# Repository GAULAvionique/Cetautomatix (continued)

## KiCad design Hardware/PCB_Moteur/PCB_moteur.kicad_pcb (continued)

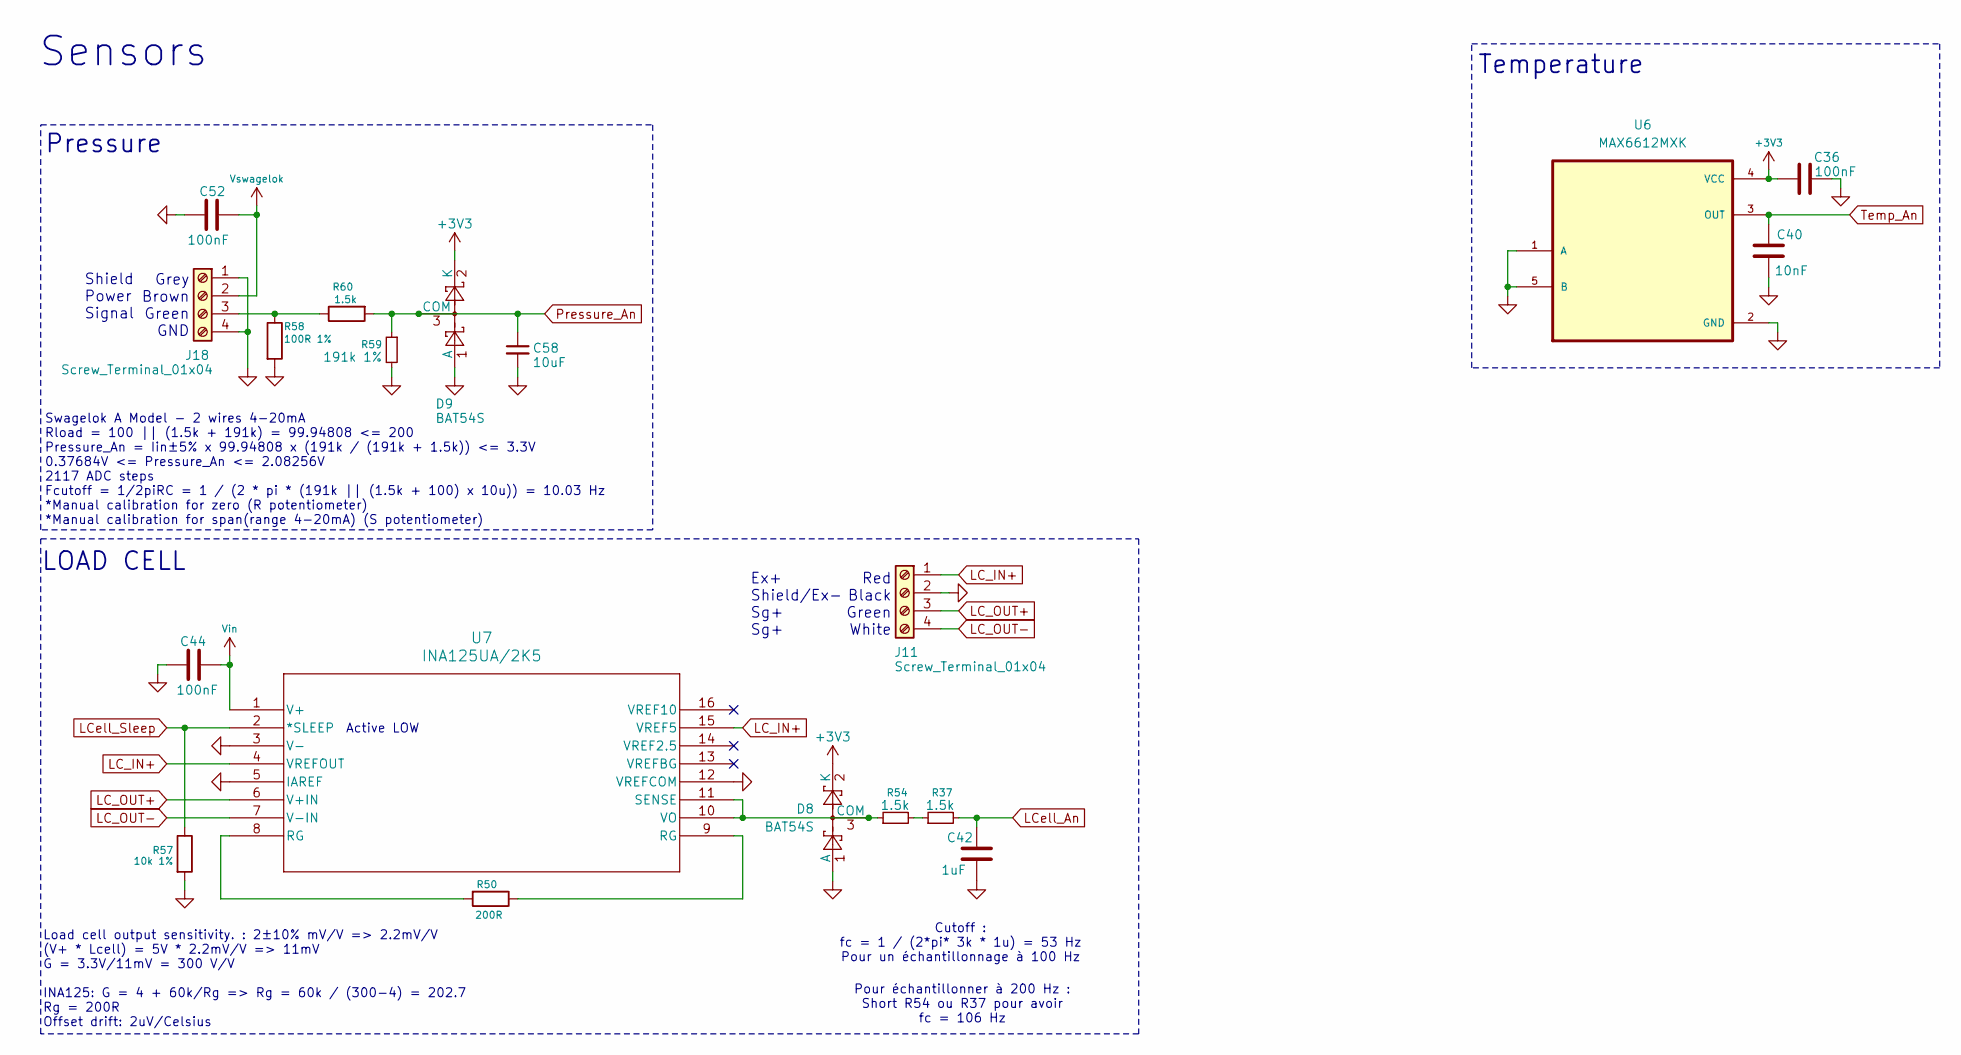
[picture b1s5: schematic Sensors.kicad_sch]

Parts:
C36, C44, C52: 100nF; C_0805_2012Metric; Manufacturer_Part_Number C0805C104K5RACTU; DigiKey_Part_Number 399-C0805C104K5RACTUCT-ND
C40: 10nF; C_0603_1608Metric; Manufacturer_Part_Number C0603C103K5RACTU; DigiKey_Part_Number 399-C0603C103K5RACTUCT-ND
C42: 1uF; C_0805_2012Metric; Manufacturer_Part_Number CL21B105KBFNNNE; DigiKey_Part_Number 1276-1029-1-ND
C58: 10uF; C_0805_2012Metric; Manufacturer_Part_Number CL21A106KAYNNNE; DigiKey_Part_Number 1276-2891-1-ND
D8, D9: BAT54S; SOT-23-3; Manufacturer_Part_Number BAT54S; DigiKey_Part_Number 4878-BAT54SCT-ND
J11, J18: Screw_Terminal_01x04; CONN_OSTVN04A150_OST; Manufacturer_Part_Number OSTVN04A150; DigiKey_Part_Number ED10563-ND
R37, R54, R60: 1.5k; R_0805_2012Metric; Manufacturer_Part_Number RC0805FR-071K5L; DigiKey_Part_Number 311-1.50KCRCT-ND
R50: 200R; R_0805_2012Metric; Manufacturer_Part_Number AC0805FR-07200RL; DigiKey_Part_Number YAG3707CT-ND
R57: 10k 1%; R_0805_2012Metric; Manufacturer_Part_Number CRCW080510K0FKEA; DigiKey_Part_Number 541-10.0KCCT-ND
R58: 100R 1%; R_0805_2012Metric; Manufacturer_Part_Number YAG3360CT-ND; DigiKey_Part_Number RT0805FRE07100RL
R59: 191k 1%; R_0805_2012Metric; Manufacturer_Part_Number RC0805FR-07191KL; DigiKey_Part_Number 311-191KCRCT-ND
U6: MAX6612MXK; SOT-353_SC-70-5; Manufacturer_Part_Number MAX6612MXK+T; DigiKey_Part_Number MAX6612MXK+TCT-ND
U7: INA125UA/2K5; D16-L; Manufacturer_Part_Number INA125UA/2K5; DigiKey_Part_Number 296-50343-1-ND

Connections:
3V3_Main: C36.1, D8.2 (K), D9.2 (K), U6.4 (VCC); also elsewhere on the board
GND: C36.2, C40.2, C42.2, C44.2, C52.1, C58.2, D8.1 (A), D9.1 (A), J11.2, J18.1, J18.4, R57.2, R58.2, R59.2, U6.1 (A), U6.2 (GND), U6.5 (B), U7.3 (V-), U7.5 (IAREF), U7.12 (VREFCOM); also elsewhere on the board
LC_IN+: J11.1, U7.4 (VREFOUT), U7.15 (VREF5)
LC_OUT+: J11.3, U7.6 (V+IN)
LC_OUT-: J11.4, U7.7 (V-IN)
LCell_An: C42.1, R37.2; also elsewhere on the board
LCell_Sleep: R57.1, U7.2 (*SLEEP); also elsewhere on the board
unnamed: D8.3 (COM), R54.1, U7.10 (VO), U7.11 (SENSE)
unnamed: J18.3, R58.1, R60.1
unnamed: R37.1, R54.2
unnamed: R50.1, U7.9 (RG)
unnamed: R50.2, U7.8 (RG)
Pressure_An: C58.1, D9.3 (COM), R59.1, R60.2; also elsewhere on the board
Temp_An: C40.1, U6.3 (OUT); also elsewhere on the board
VIN_Filtered: C44.1, U7.1 (V+); also elsewhere on the board
Vswagelok: C52.2, J18.2; also elsewhere on the board

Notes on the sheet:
Temperature
Cutoff : fc = 1 / (2*pi* 3k * 1u) = 53 Hz Pour un échantillonnage à 100 Hz
Active LOW
Load cell output sensitivity. : 2±10% mV/V => 2.2mV/V (V+ * Lcell) = 5V * 2.2mV/V => 11mV G = 3.3V/11mV = 300 V/V INA125: G = 4 + 60k/Rg => Rg = 60k / (300-4) = 202.7 Rg = 200R Offset drift: 2uV/Celsius
Red Black Green White
Ex+ Shield/Ex- Sg+ Sg+
Shield Power Signal
Grey Brown Green GND
LOAD CELL
Pour échantillonner à 200 Hz : Short R54 ou R37 pour avoir fc = 106 Hz
Sensors
Swagelok A Model - 2 wires 4-20mA Rload = 100 || (1.5k + 191k) = 99.94808 <= 200 Pressure_An = Iin±5% x 99.94808 x (191k / (191k + 1.5k)) <= 3.3V 0.37684V <= Pressure_An <= 2.08256V 2117 ADC steps Fcutoff = 1/2piRC = 1 / (2 * pi * (191k || (1.5k + 100) x 10u)) = 10.03 Hz *Manual calibration for zer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
Pressure

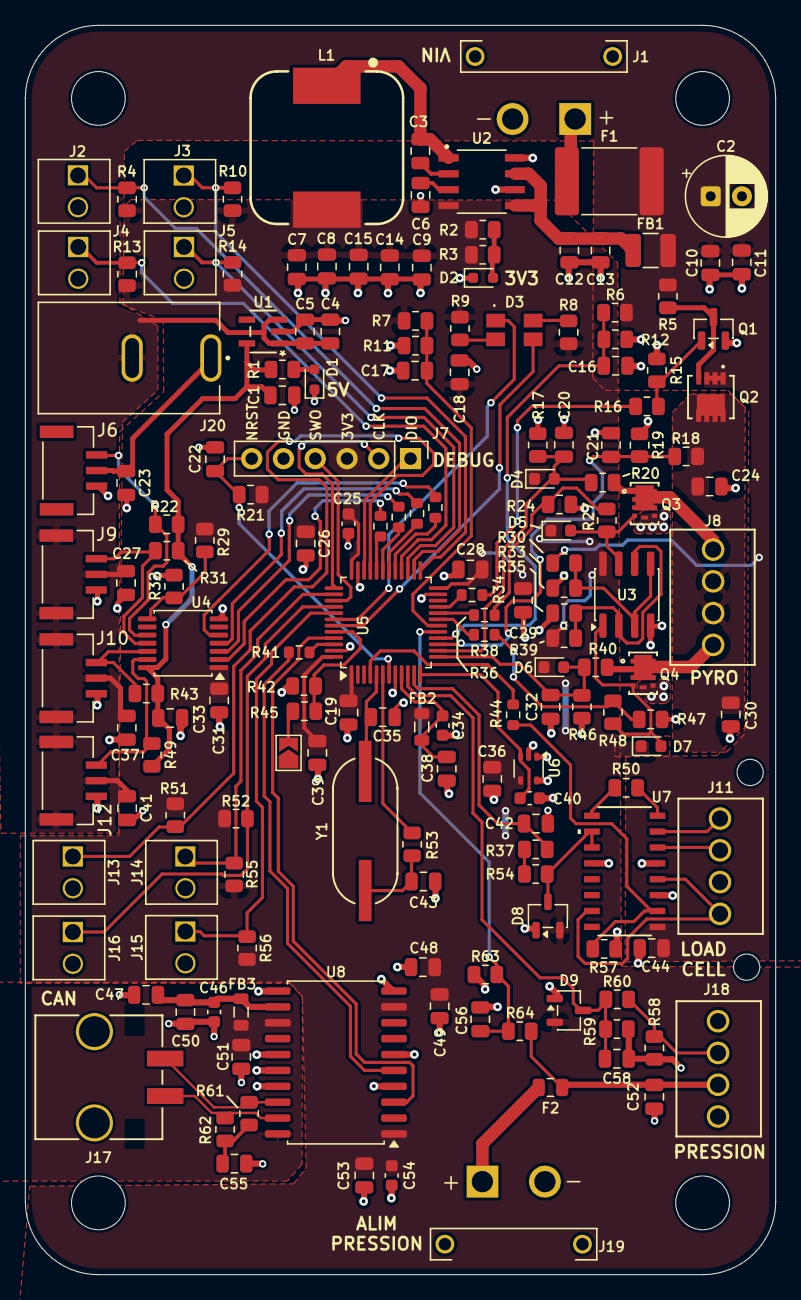
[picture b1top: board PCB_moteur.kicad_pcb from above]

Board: 2 copper layers, 60.0 x 99.9 mm, 173 parts (0 on the bottom side), 92 nets.

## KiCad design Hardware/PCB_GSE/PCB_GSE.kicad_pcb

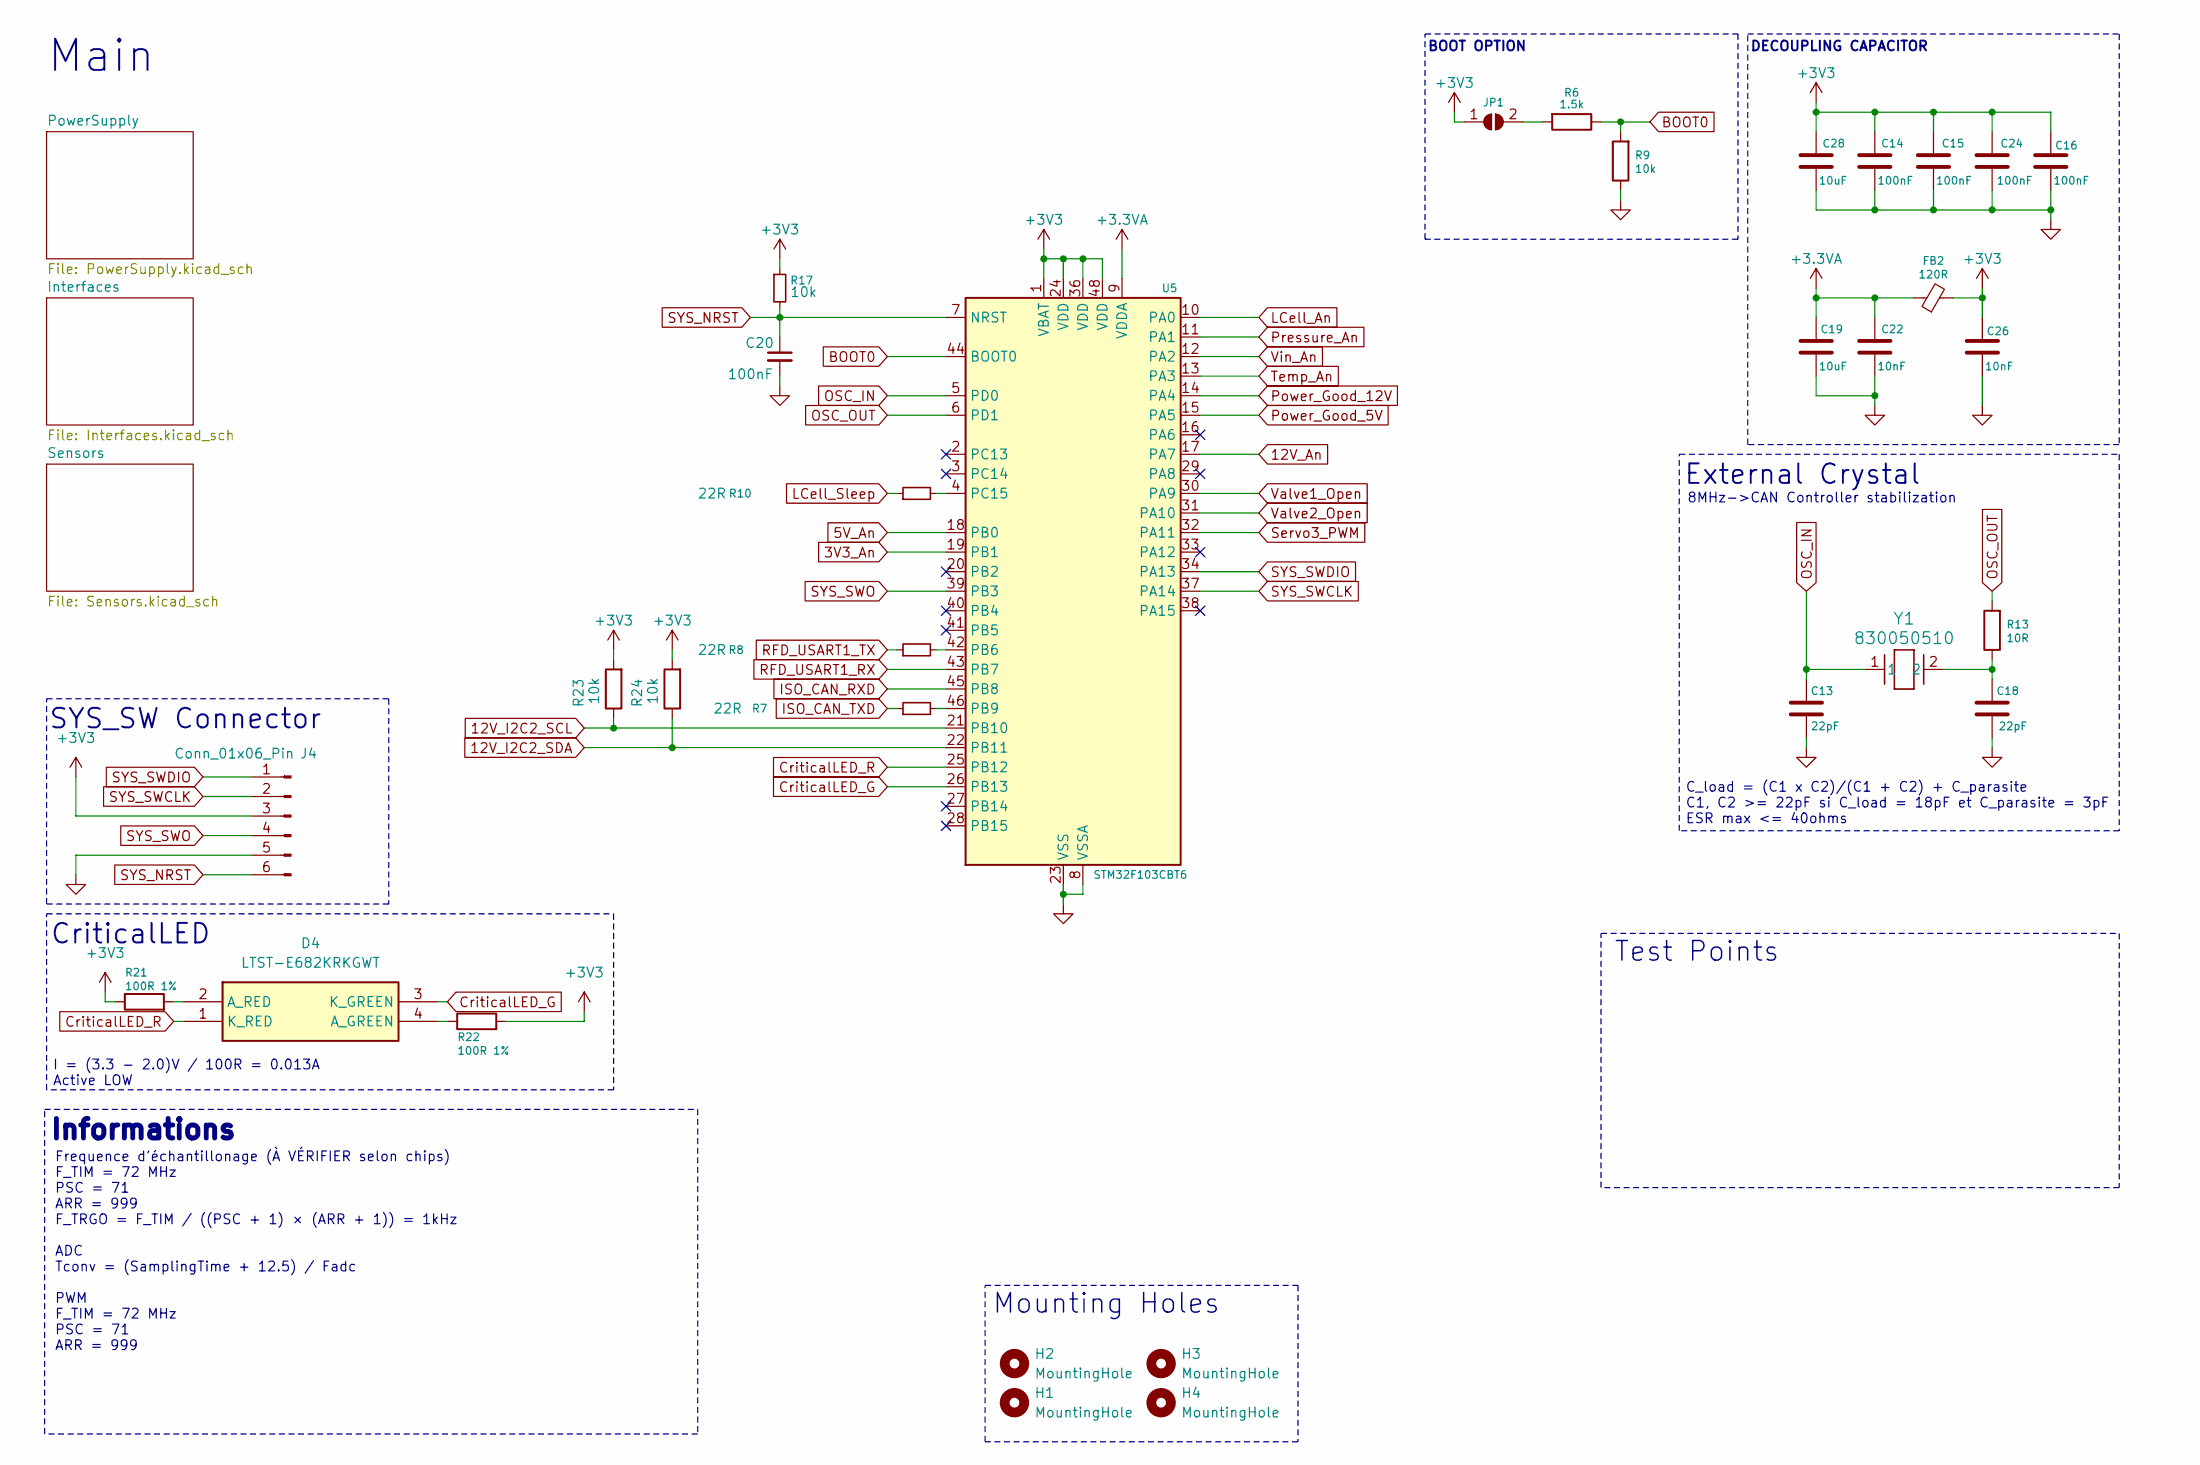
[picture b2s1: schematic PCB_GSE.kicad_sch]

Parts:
C13, C18: 22pF; C_0805_2012Metric; Manufacturer_Part_Number QSCT251Q220F1GV001E; DigiKey_Part_Number 712-QSCT251Q220F1GV001ECT-ND
C14, C15, C16, C20, C24: 100nF; C_0603_1608Metric; Manufacturer_Part_Number C0603C104K3RACTU; DigiKey_Part_Number 399-C0603C104K3RACTUCT-ND
C19, C28: 10uF; C_0805_2012Metric; Manufacturer_Part_Number CL21A106KAYNNNE; DigiKey_Part_Number 1276-2891-1-ND
C22, C26: 10nF; C_0805_2012Metric; Manufacturer_Part_Number CL21B103KAANNNC; DigiKey_Part_Number 1276-2434-1-ND
D4: LTST-E682KRKGWT; LTSTE683RGBW; Mouser Part Number 859-LTST-E682KRKGWT
FB2: 120R; L_0805_2012Metric; Manufacturer_Part_Number 2508051217Y6; DigiKey_Part_Number 1934-1472-1-ND
H1, H2, H3, H4: MountingHole; MountingHole_4.3mm_M4
J4: Conn_01x06_Pin; PinHeader_1x06_P2.54mm_Vertical; Manufacturer_Part_Number 61300611121; DigiKey_Part_Number 732-5319-ND
JP1: SolderJumper_2_Open; SolderJumper-2_P1.3mm_Open_TrianglePad1.0x1.5mm
R6: 1.5k; R_0805_2012Metric; Manufacturer_Part_Number RC0805FR-071K5L; DigiKey_Part_Number 311-1.50KCRCT-ND
R7, R8, R10: 22R; R_0603_1608Metric; Manufacturer_Part_Number ESR03EZPJ220; DigiKey_Part_Number RHM22DCT-ND
R9, R17, R23, R24: 10k; R_0805_2012Metric; Manufacturer_Part_Number CRCW080510K0FKEA; DigiKey_Part_Number 541-10.0KCCT-ND
R13: 10R; R_0805_2012Metric; Manufacturer_Part_Number RC0805FR-0710RL; DigiKey_Part_Number 311-10.0CRCT-ND
R21, R22: 100R 1%; R_0805_2012Metric; Manufacturer_Part_Number YAG3360CT-ND; DigiKey_Part_Number RT0805FRE07100RL
U5: STM32F103CBT6; LQFP-48_7x7mm_P0.5mm; Manufacturer_Part_Number STM32F103CBT6; DigiKey_Part_Number 497-6288-ND
Y1: 830050510; Manufacturer_Part_Number 830050510; DigiKey_Part_Number 1923-830050510CT-ND

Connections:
3V3_An: U5.19 (PB1); also elsewhere on the board
3V_Main: C14.2, C15.2, C16.2, C24.2, C26.2, C28.2, FB2.2, J4.3, JP1.1 (A), R17.1, R21.1, R22.2, R23.2, R24.2, U5.1 (VBAT), U5.24 (VDD), U5.36 (VDD), U5.48 (VDD); also elsewhere on the board
5V_An: U5.18 (PB0); also elsewhere on the board
12V_An: U5.17 (PA7); also elsewhere on the board
12V_I2C2_SCL: R23.1, U5.21 (PB10); also elsewhere on the board
12V_I2C2_SDA: R24.1, U5.22 (PB11); also elsewhere on the board
+3.3VA: C19.2, C22.2, FB2.1, U5.9 (VDDA)
BOOT0: R6.1, R9.2, U5.44 (BOOT0)
CriticalLED_G: D4.3 (K_GREEN), U5.26 (PB13)
CriticalLED_R: D4.1 (K_RED), U5.25 (PB12)
GND: C13.1, C14.1, C15.1, C16.1, C18.1, C19.1, C20.2, C22.1, C24.1, C26.1, C28.1, J4.5, R9.1, U5.8 (VSSA), U5.23 (VSS), U5.35 (VSS), U5.47 (VSS); also elsewhere on the board
ISO_CAN_RXD: U5.45 (PB8); also elsewhere on the board
ISO_CAN_TXD: R7.1; also elsewhere on the board
LCell_An: U5.10 (PA0); also elsewhere on the board
LCell_Sleep: R10.1; also elsewhere on the board
unnamed: C18.2, R13.1, Y1.2
unnamed: D4.4 (A_GREEN), R22.1
unnamed: D4.2 (A_RED), R21.2
unnamed: JP1.2 (B), R6.2
unnamed: R8.2, U5.42 (PB6)
unnamed: R7.2, U5.46 (PB9)
unnamed: R10.2, U5.4 (PC15)
OSC_IN: C13.2, U5.5 (PD0), Y1.1
OSC_OUT: R13.2, U5.6 (PD1)
Power_Good_5V: U5.15 (PA5); also elsewhere on the board
Power_Good_12V: U5.14 (PA4); also elsewhere on the board
Pressure_An: U5.11 (PA1); also elsewhere on the board
RFD_USART1_RX: U5.43 (PB7); also elsewhere on the board
RFD_USART1_TX: R8.1; also elsewhere on the board
SYS_NRST: C20.1, J4.6, R17.2, U5.7 (NRST)
SYS_SWCLK: J4.2, U5.37 (PA14)
SYS_SWDIO: J4.1, U5.34 (PA13)
SYS_SWO: J4.4, U5.39 (PB3)
Servo3_PWM: U5.32 (PA11); also elsewhere on the board
Temp_An: U5.13 (PA3); also elsewhere on the board
Valve1_Open: U5.30 (PA9); also elsewhere on the board
Valve2_Open: U5.31 (PA10); also elsewhere on the board
Vin_An: U5.12 (PA2); also elsewhere on the board

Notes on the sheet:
BOOT OPTION
SYS_SW Connector
I = (3.3 - 2.0)V / 100R = 0.013A Active LOW
CriticalLED
Test Points
External Crystal
Informations
C_load = (C1 x C2)/(C1 + C2) + C_parasite C1, C2 >= 22pF si C_load = 18pF et C_parasite = 3pF ESR max <= 40ohms
Main
8MHz->CAN Controller stabilization
DECOUPLING CAPACITOR
Frequence d'échantillonage (À VÉRIFIER selon chips) F_TIM = 72 MHz PSC = 71 ARR = 999 F_TRGO = F_TIM / ((PSC + 1) × (ARR + 1)) = 1kHz ADC Tconv = (SamplingTime + 12.5) / Fadc PWM F_TIM = 72 MHz PSC = 71 ARR = 999
Mounting Holes

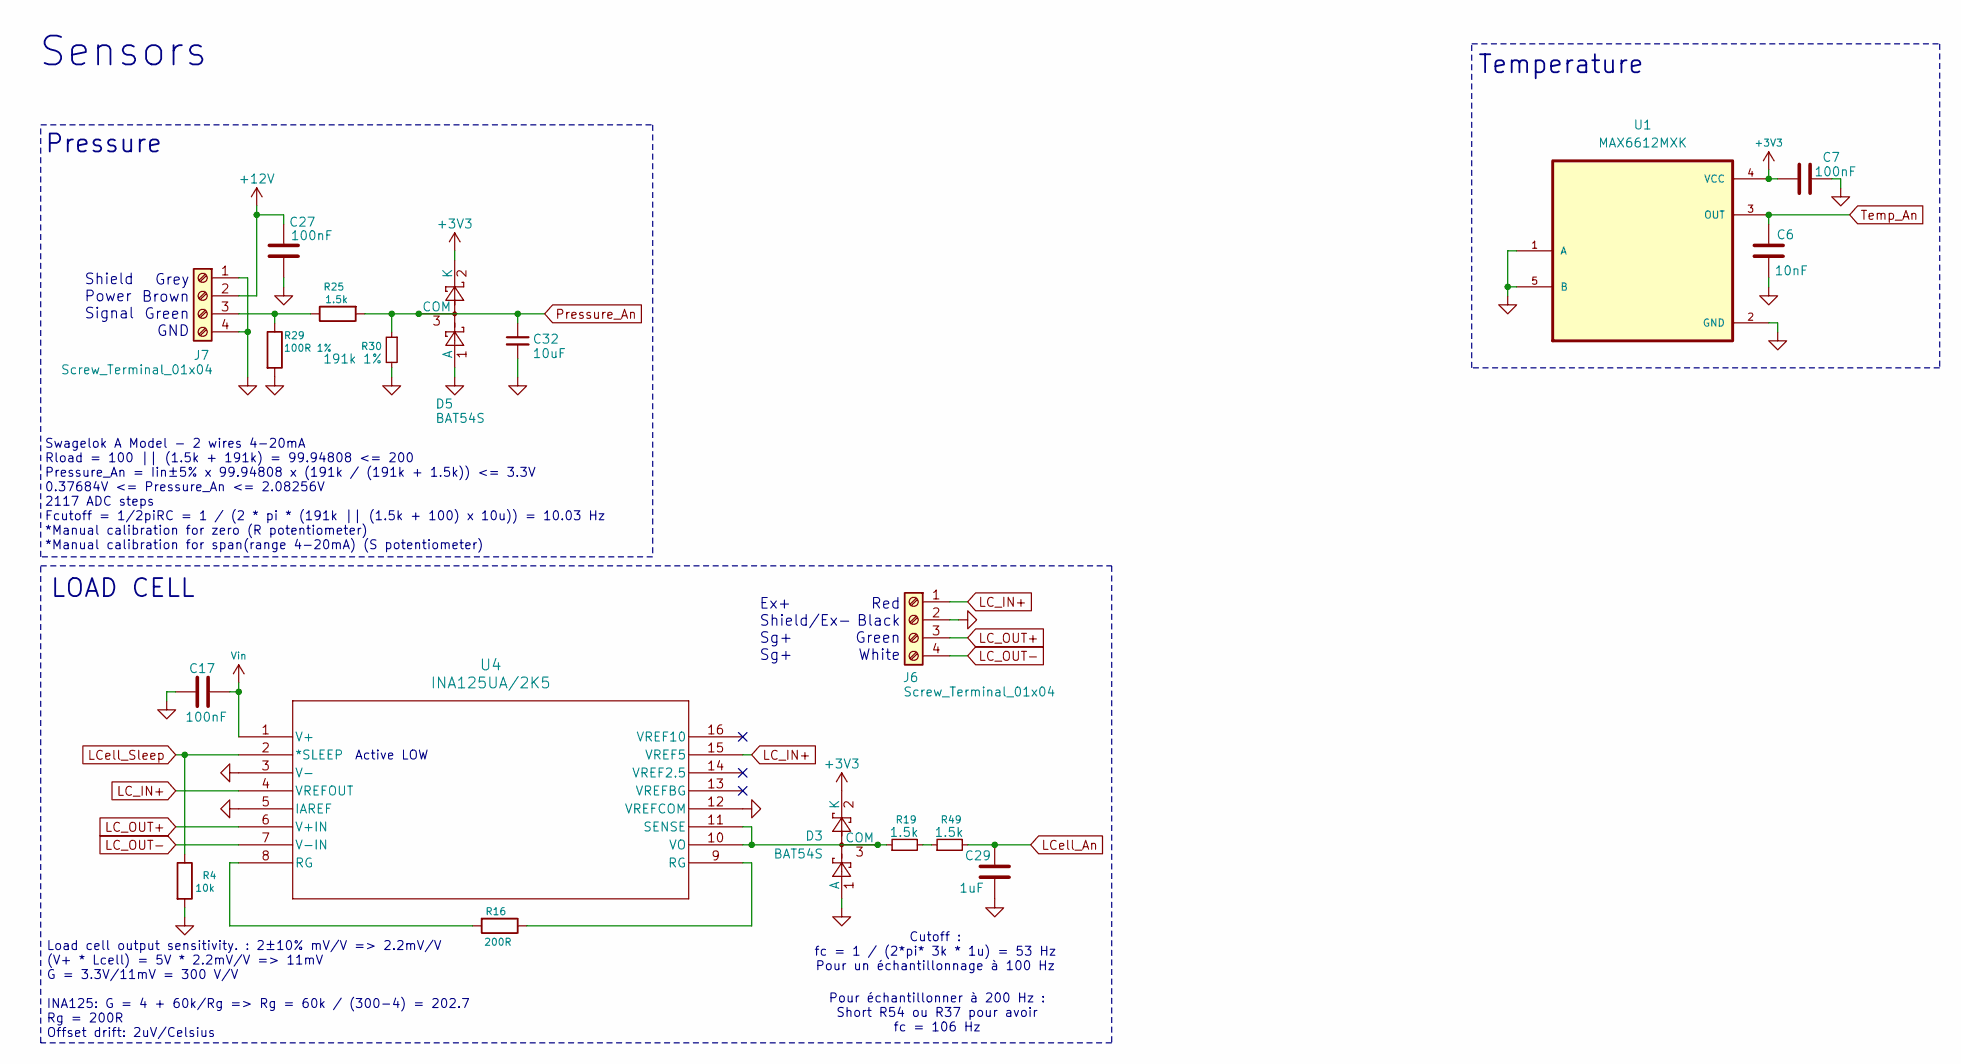
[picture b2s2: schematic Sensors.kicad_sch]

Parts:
C6: 10nF; C_0805_2012Metric; Manufacturer_Part_Number CL21B103KAANNNC; DigiKey_Part_Number 1276-2434-1-ND
C7, C17, C27: 100nF; C_0603_1608Metric; Manufacturer_Part_Number C0603C104K3RACTU; DigiKey_Part_Number 399-C0603C104K3RACTUCT-ND
C29: 1uF; C_0805_2012Metric; Manufacturer_Part_Number CL21B105KBFNNNE; DigiKey_Part_Number 1276-1029-1-ND
C32: 10uF; C_0805_2012Metric; Manufacturer_Part_Number CL21A106KAYNNNE; DigiKey_Part_Number 1276-2891-1-ND
D3, D5: BAT54S; SOT-23-3; Manufacturer_Part_Number BAT54S; DigiKey_Part_Number 4878-BAT54SCT-ND
J6, J7: Screw_Terminal_01x04; CONN_OSTVN04A150_OST; Manufacturer_Part_Number OSTVN04A150; DigiKey_Part_Number ED10563-ND
R4: 10k; R_0805_2012Metric; Manufacturer_Part_Number CRCW080510K0FKEA; DigiKey_Part_Number 541-10.0KCCT-ND
R16: 200R; R_0805_2012Metric; Manufacturer_Part_Number AC0805FR-07200RL; DigiKey_Part_Number YAG3707CT-ND
R19, R25, R49: 1.5k; R_0805_2012Metric; Manufacturer_Part_Number RC0805FR-071K5L; DigiKey_Part_Number 311-1.50KCRCT-ND
R29: 100R 1%; R_0805_2012Metric; Manufacturer_Part_Number YAG3360CT-ND; DigiKey_Part_Number RT0805FRE07100RL
R30: 191k 1%; R_0805_2012Metric; Manufacturer_Part_Number RC0805FR-07191KL; DigiKey_Part_Number 311-191KCRCT-ND
U1: MAX6612MXK; SOT-353_SC-70-5; Manufacturer_Part_Number MAX6612MXK+T; DigiKey_Part_Number MAX6612MXK+TCT-ND
U4: INA125UA/2K5; D16-L; Manufacturer_Part_Number INA125UA/2K5; DigiKey_Part_Number 296-50343-1-ND

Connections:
3V_Main: C7.1, D3.2 (K), D5.2 (K), U1.4 (VCC); also elsewhere on the board
GND: C6.2, C7.2, C17.2, C27.2, C29.2, C32.2, D3.1 (A), D5.1 (A), J6.2, J7.1, J7.4, R4.2, R29.2, R30.2, U1.1 (A), U1.2 (GND), U1.5 (B), U4.3 (V-), U4.5 (IAREF), U4.12 (VREFCOM); also elsewhere on the board
LC_IN+: J6.1, U4.4 (VREFOUT), U4.15 (VREF5)
LC_OUT+: J6.3, U4.6 (V+IN)
LC_OUT-: J6.4, U4.7 (V-IN)
LCell_An: C29.1, R49.2; also elsewhere on the board
LCell_Sleep: R4.1, U4.2 (*SLEEP); also elsewhere on the board
unnamed: D3.3 (COM), R19.1, U4.10 (VO), U4.11 (SENSE)
unnamed: J7.3, R25.1, R29.1
unnamed: R16.1, U4.9 (RG)
unnamed: R16.2, U4.8 (RG)
unnamed: R19.2, R49.1
Pressure_An: C32.1, D5.3 (COM), R25.2, R30.1; also elsewhere on the board
Temp_An: C6.1, U1.3 (OUT); also elsewhere on the board
VIN_Filtered: C17.1, U4.1 (V+); also elsewhere on the board
Vin_Valve: C27.1, J7.2; also elsewhere on the board

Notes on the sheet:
Load cell output sensitivity. : 2±10% mV/V => 2.2mV/V (V+ * Lcell) = 5V * 2.2mV/V => 11mV G = 3.3V/11mV = 300 V/V INA125: G = 4 + 60k/Rg => Rg = 60k / (300-4) = 202.7 Rg = 200R Offset drift: 2uV/Celsius
Temperature
LOAD CELL
Pressure
Pour échantillonner à 200 Hz : Short R54 ou R37 pour avoir fc = 106 Hz
Swagelok A Model - 2 wires 4-20mA Rload = 100 || (1.5k + 191k) = 99.94808 <= 200 Pressure_An = Iin±5% x 99.94808 x (191k / (191k + 1.5k)) <= 3.3V 0.37684V <= Pressure_An <= 2.08256V 2117 ADC steps Fcutoff = 1/2piRC = 1 / (2 * pi * (191k || (1.5k + 100) x 10u)) = 10.03 Hz *Manual calibration for zer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
Red Black Green White
Shield Power Signal
Sensors
Cutoff : fc = 1 / (2*pi* 3k * 1u) = 53 Hz Pour un échantillonnage à 100 Hz
Grey Brown Green GND
Ex+ Shield/Ex- Sg+ Sg+
Active LOW

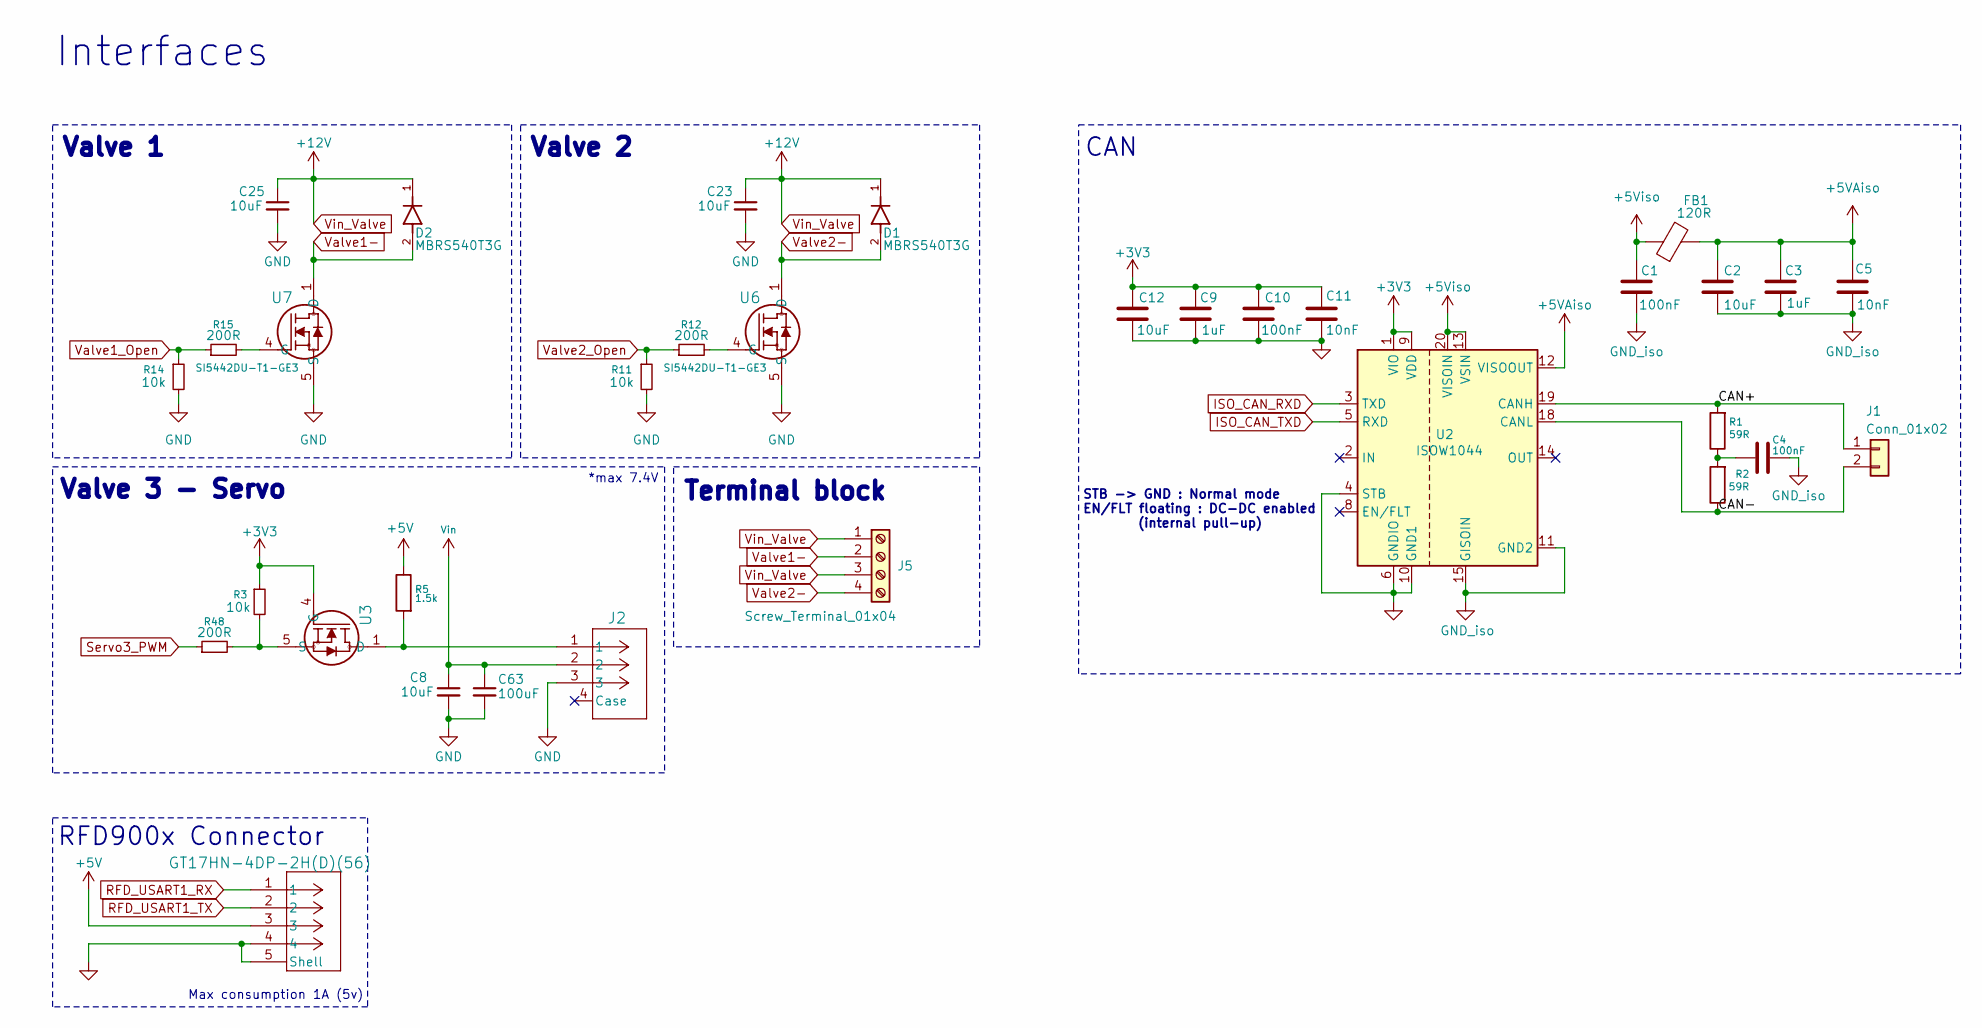
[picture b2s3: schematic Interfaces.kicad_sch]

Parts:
C1, C4, C10: 100nF; C_0603_1608Metric; Manufacturer_Part_Number C0603C104K3RACTU; DigiKey_Part_Number 399-C0603C104K3RACTUCT-ND
C2, C8, C12, C23, C25: 10uF; C_0805_2012Metric; Manufacturer_Part_Number CL21A106KAYNNNE; DigiKey_Part_Number 1276-2891-1-ND
C3, C9: 1uF; C_0805_2012Metric; Manufacturer_Part_Number CL21B105KBFNNNE; DigiKey_Part_Number 1276-1029-1-ND
C5, C11: 10nF; C_0805_2012Metric; Manufacturer_Part_Number CL21B103KAANNNC; DigiKey_Part_Number 1276-2434-1-ND
C63: 100uF; U2-K_NCH; Manufacturer_Part_Number UCL1E101MCL1GS; DigiKey_Part_Number 493-3937-1-ND
D1, D2: MBRS540T3G; DIODE_SMB_2L_ONS; PARTREV 7/27/2017; DigiKey_Part_Number MBRS130LT3GOSCT-ND
FB1: 120R; L_0805_2012Metric; Manufacturer_Part_Number 2508051217Y6; DigiKey_Part_Number 1934-1472-1-ND
J1: Conn_01x02; CONN_2189890010-SD_02_MOL; Manufacturer_Part_Number 2189890210; DigiKey_Part_Number 900-2189890210CT-ND
J2: SM03B-GHS-TB; JST_SM03B-GHS-TB; Manufacturer_Part_Number SM03B-GHS-TB; DigiKey_Part_Number 455-SM03B-GHS-TBCT-ND
J3: GT17HN-4DP-2H(D)(56); CONN4_GT17HN_HIR; Manufacturer_Part_Number GT17HN-4DP-2H(D)(56); DigiKey_Part_Number 26-GT17HN-4DP-2H(D)(56)-ND
J5: Screw_Terminal_01x04; CONN_OSTVN04A150_OST; Manufacturer_Part_Number OSTVN04A150; DigiKey_Part_Number ED10563-ND
R1, R2: 59R; R_0805_2012Metric; Manufacturer_Part_Number RC0805FR-0759RL; DigiKey_Part_Number 311-59.0CRCT-ND
R3, R11, R14: 10k; R_0805_2012Metric; Manufacturer_Part_Number CRCW080510K0FKEA; DigiKey_Part_Number 541-10.0KCCT-ND
R5: 1.5k; R_0805_2012Metric; Manufacturer_Part_Number RC0805FR-071K5L; DigiKey_Part_Number 311-1.50KCRCT-ND
R12, R15, R48: 200R; R_0805_2012Metric; Manufacturer_Part_Number AC0805FR-07200RL; DigiKey_Part_Number YAG3707CT-ND
U2: ISOW1044; SOIC-20W_7.5x12.8mm_P1.27mm; Manufacturer_Part_Number ISOW1044BDFMR; DigiKey_Part_Number 296-ISOW1044BDFMRCT-ND
U3, U6, U7: SI5442DU-T1-GE3; SI5442DU_T1_G3; Manufacturer_Part_Number SI5442DU-T1-GE3; DigiKey_Part_Number SI5442DU-T1-GE3CT-ND

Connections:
3V_Main: C9.1, C10.1, C11.1, C12.1, R3.1, U2.1 (VIO), U2.9 (VDD), U3.4 (G); also elsewhere on the board
5V_Main: J3.3, R5.1; also elsewhere on the board
+5VAiso: C2.1, C3.1, C5.1, FB1.2, U2.12 (VISOOUT)
+5Viso: C1.1, FB1.1, U2.13 (VSIN), U2.20 (VISOIN)
/Interfaces/CAN+: J1.1, R1.2, U2.19 (CANH)
/Interfaces/CAN-: J1.2, R2.1, U2.18 (CANL)
GND: C8.2, C9.2, C10.2, C11.2, C12.2, C23.2, C25.2, C63.2, J2.3, J3.4, J3.5 (Shell), R11.2, R14.2, U2.4 (STB), U2.6 (GNDIO), U2.10 (GND1), U6.5 (S), U6.9 (S), U7.5 (S), U7.9 (S); also elsewhere on the board
GND_iso: C1.2, C2.2, C3.2, C4.2, C5.2, U2.11 (GND2), U2.15 (GISOIN), U2.16 (GISOIN), U2.17 (GISOIN)
ISO_CAN_RXD: U2.3 (TXD); also elsewhere on the board
ISO_CAN_TXD: U2.5 (RXD); also elsewhere on the board
unnamed: C4.1, R1.1, R2.2
unnamed: J2.1, R5.2, U3.1 (D), U3.2 (D), U3.3 (D), U3.6 (D), U3.7 (D), U3.8 (D)
unnamed: R3.2, R48.2, U3.5 (S), U3.9 (S)
unnamed: R12.2, U6.4 (G)
unnamed: R15.2, U7.4 (G)
RFD_USART1_RX: J3.1; also elsewhere on the board
RFD_USART1_TX: J3.2; also elsewhere on the board
Servo3_PWM: R48.1; also elsewhere on the board
VIN_Filtered: C8.1, C63.1, J2.2; also elsewhere on the board
Valve1-: D2.2, J5.2, U7.1 (D), U7.2 (D), U7.3 (D), U7.6 (D), U7.7 (D), U7.8 (D)
Valve1_Open: R14.1, R15.1; also elsewhere on the board
Valve2-: D1.2, J5.4, U6.1 (D), U6.2 (D), U6.3 (D), U6.6 (D), U6.7 (D), U6.8 (D)
Valve2_Open: R11.1, R12.1; also elsewhere on the board
Vin_Valve: C23.1, C25.1, D1.1, D2.1, J5.1, J5.3; also elsewhere on the board

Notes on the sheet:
Max consumption 1A (5v)
Valve 3 - Servo
Interfaces
*max 7.4V
STB -> GND : Normal mode EN/FLT floating : DC-DC enabled (internal pull-up)
Valve 2
Valve 1
RFD900x Connector
Terminal block
CAN
